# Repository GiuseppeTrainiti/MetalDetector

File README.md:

# MetalDetector

In order to open the code you need to have MDK-ARM Keil installed.
Once you install it, you can open the project:

Metaldetector/Code/Metaldetector/MDK-ARM/metalDetector_comInterface.uvprojx

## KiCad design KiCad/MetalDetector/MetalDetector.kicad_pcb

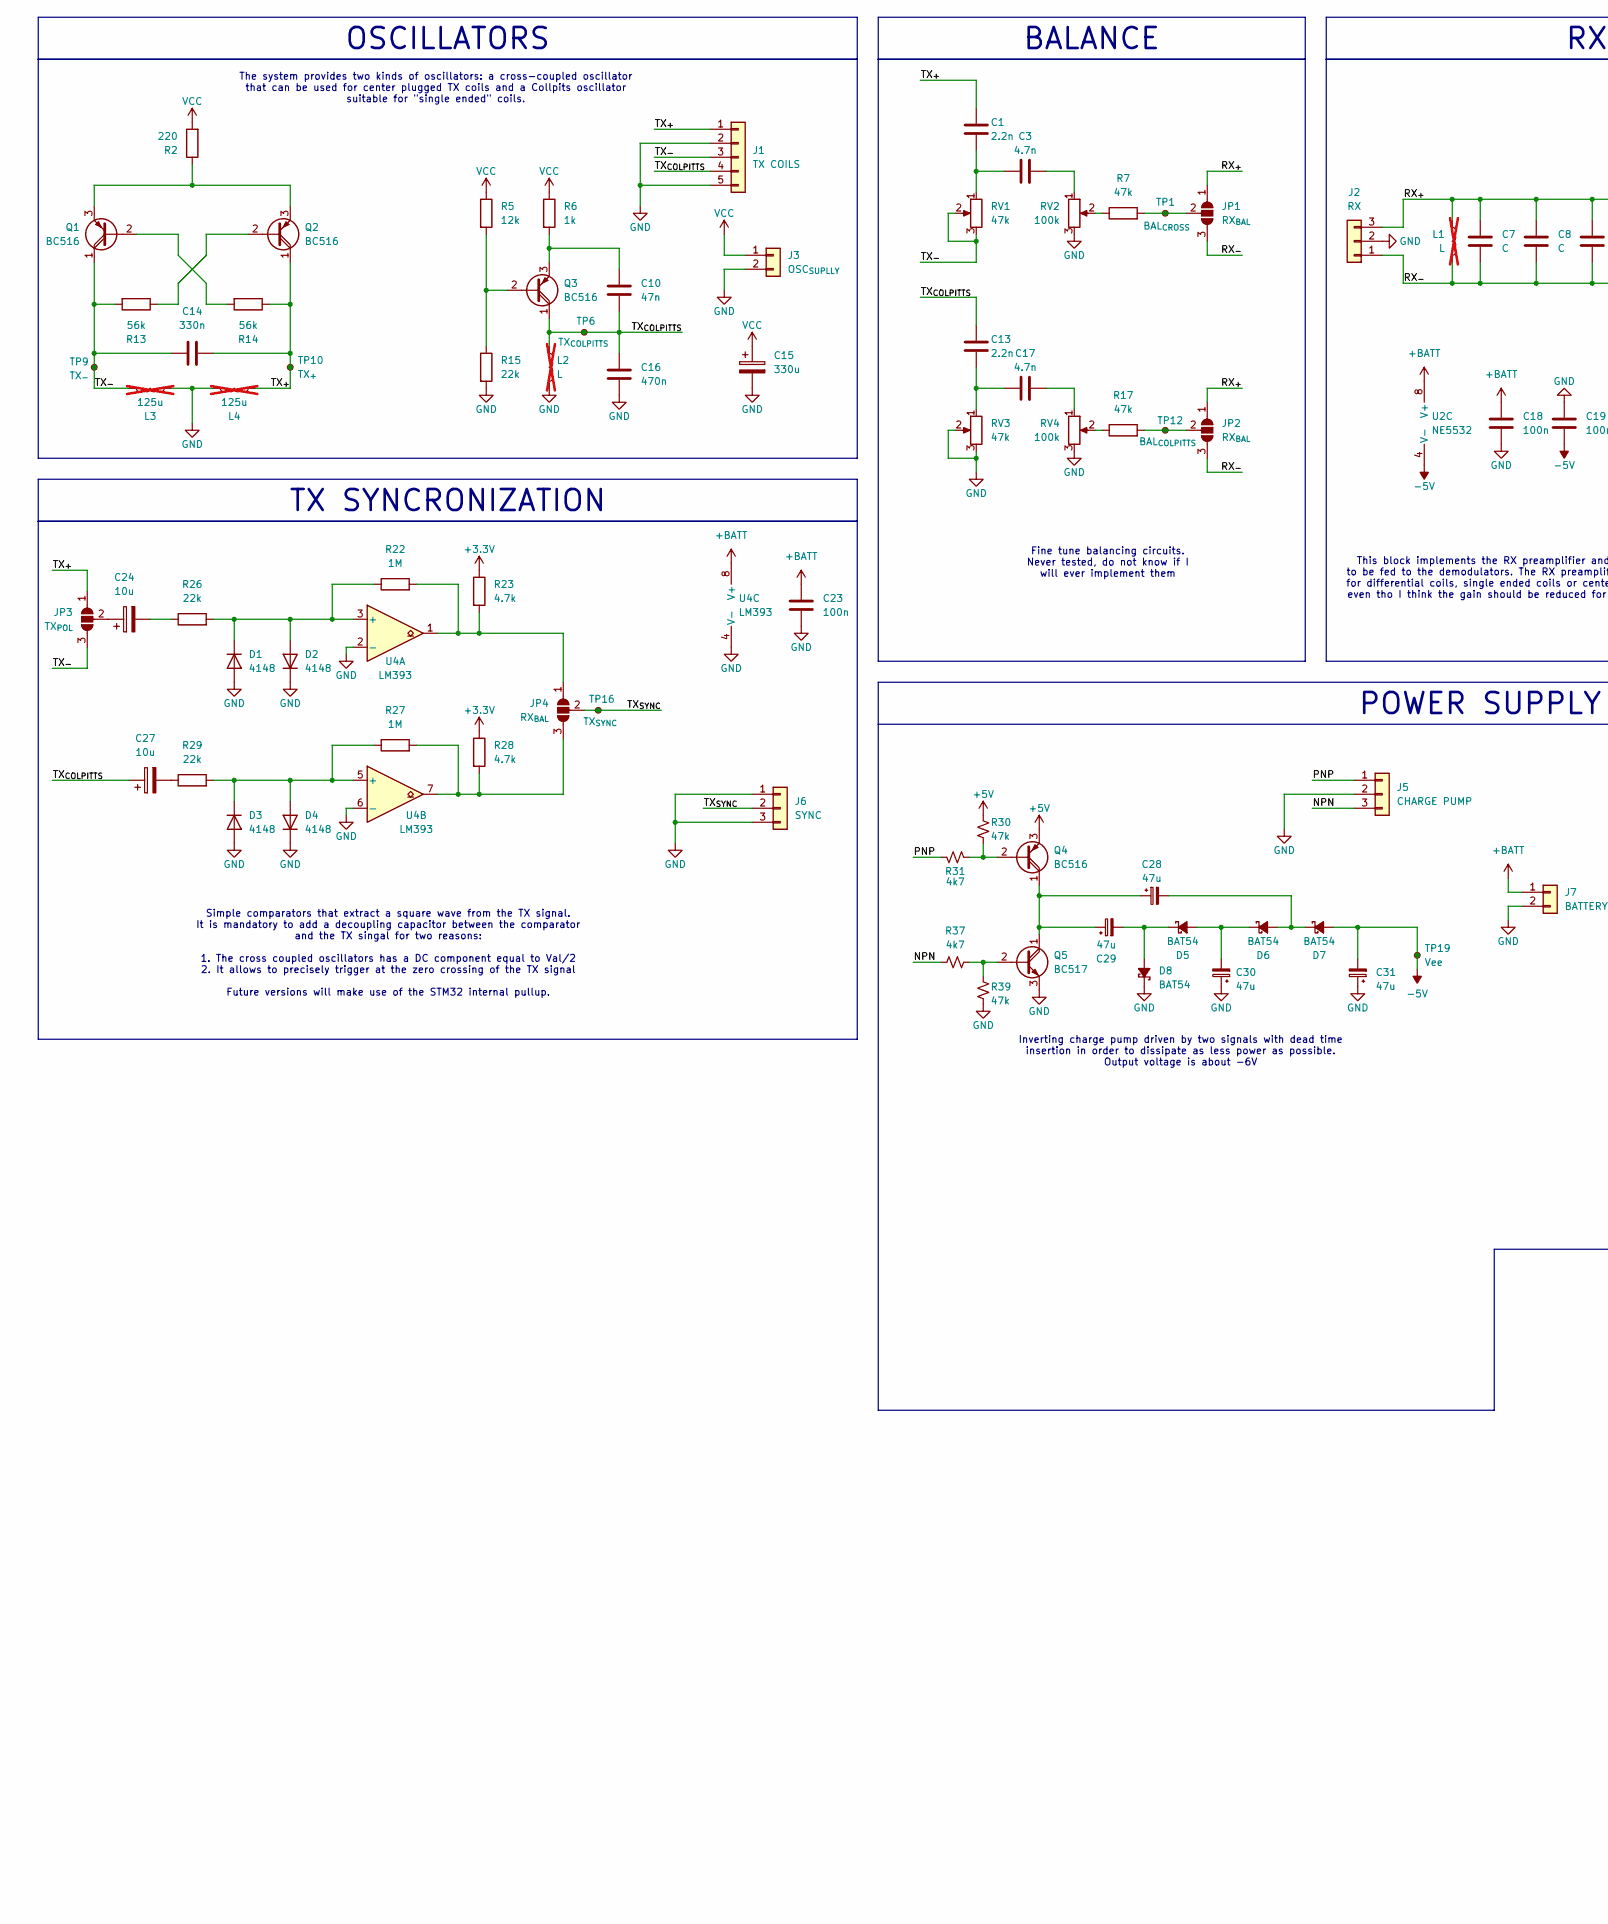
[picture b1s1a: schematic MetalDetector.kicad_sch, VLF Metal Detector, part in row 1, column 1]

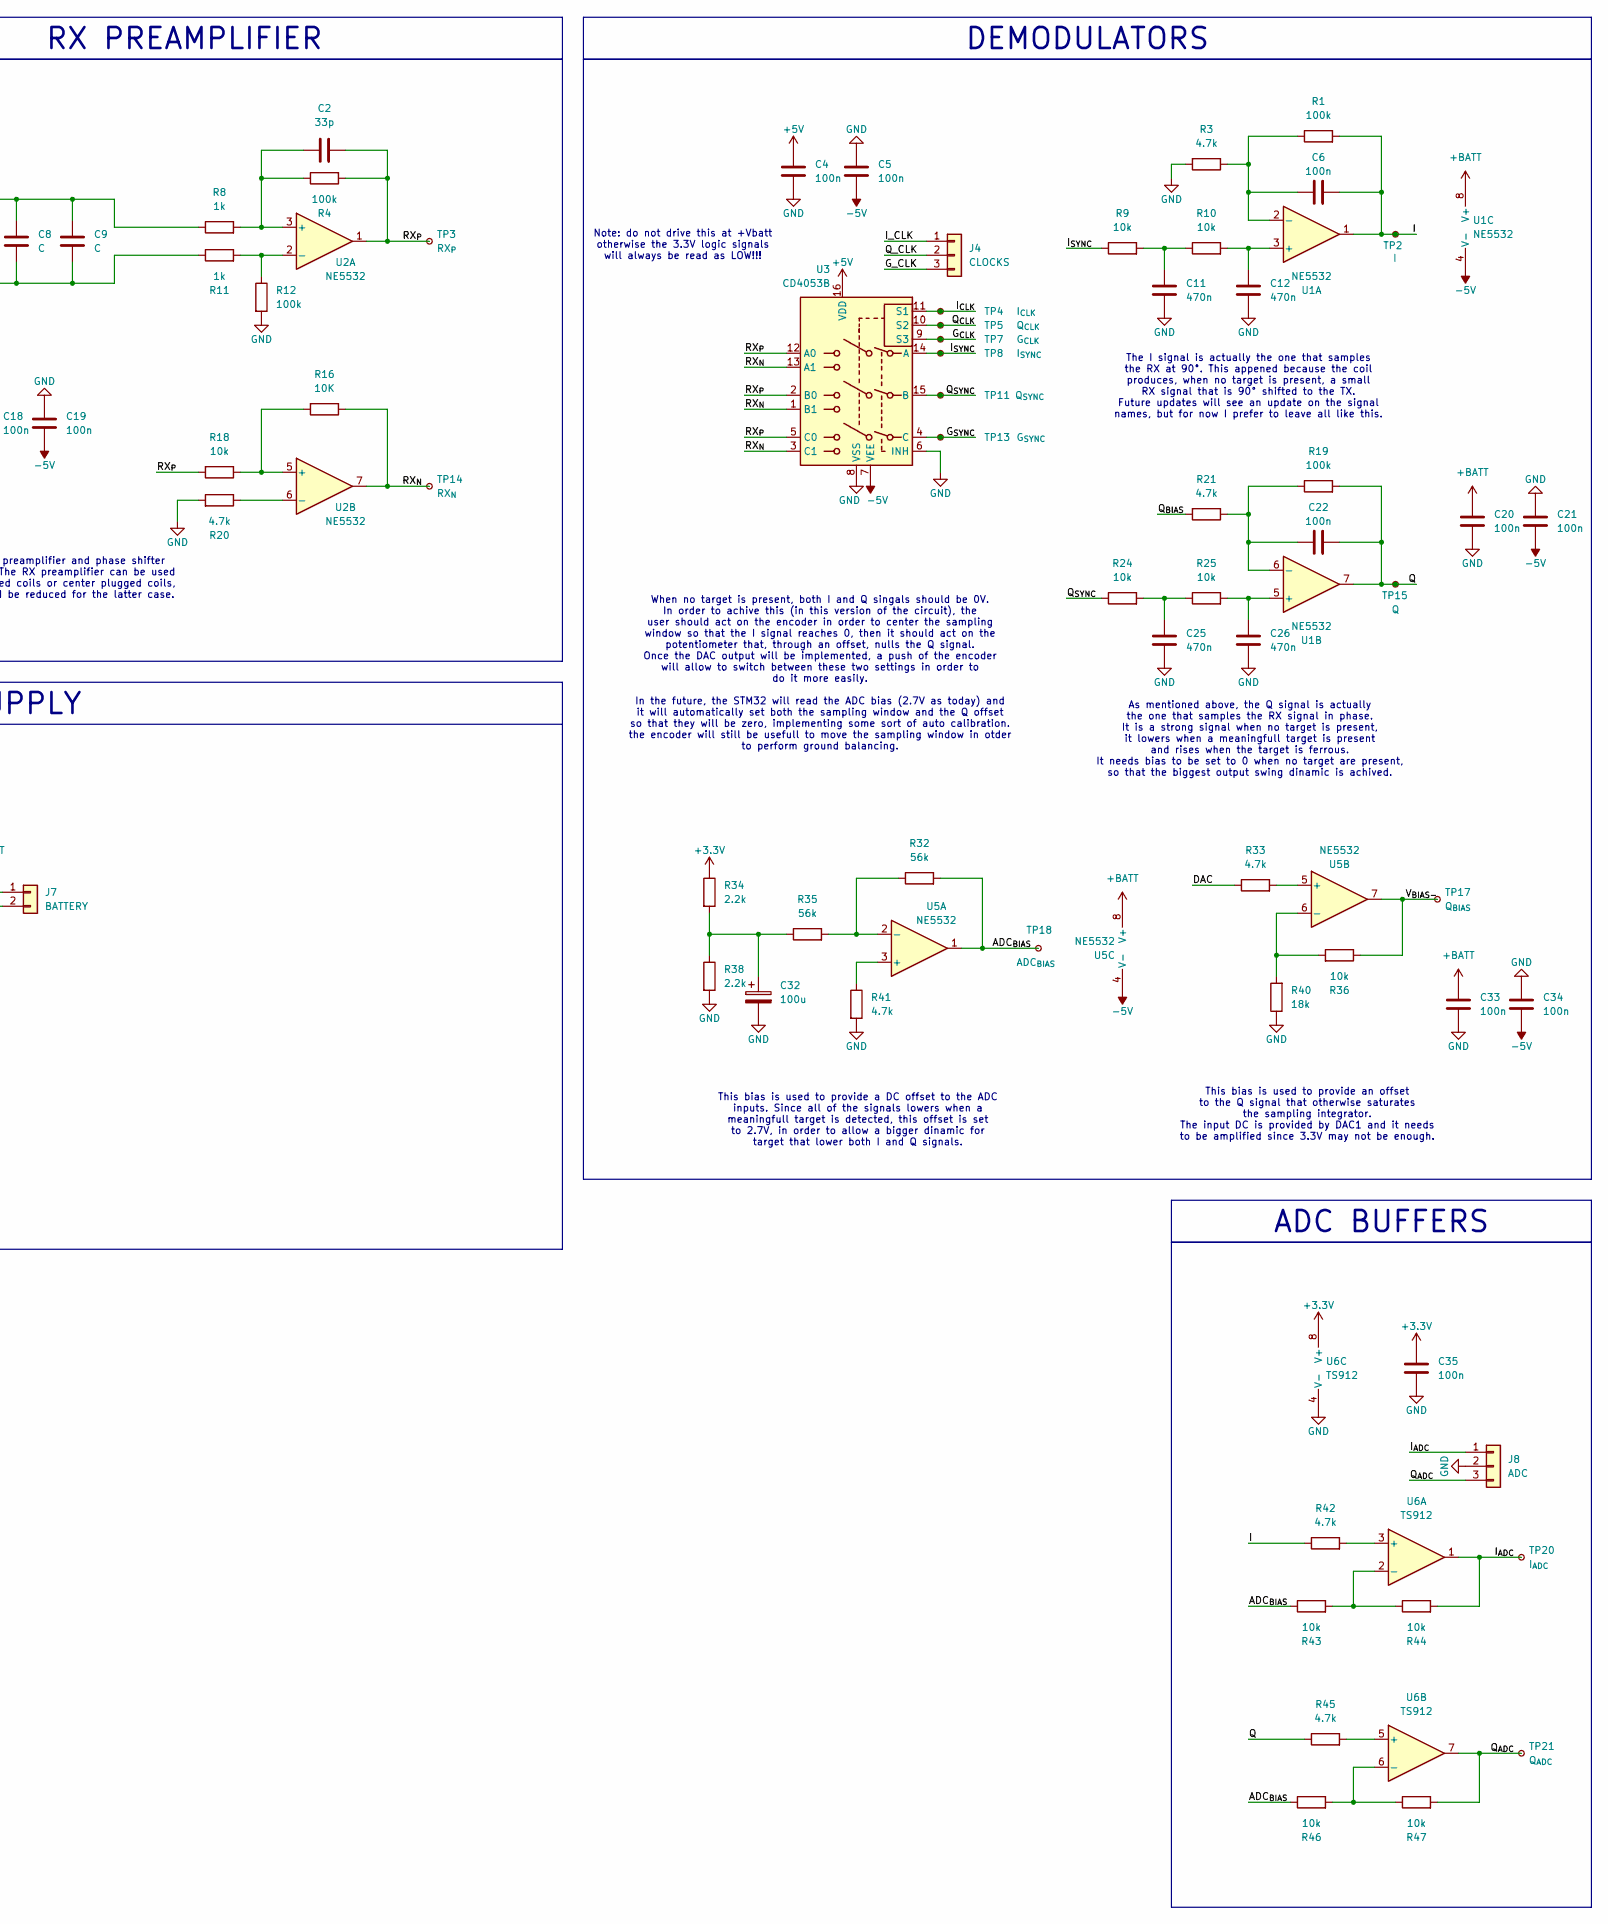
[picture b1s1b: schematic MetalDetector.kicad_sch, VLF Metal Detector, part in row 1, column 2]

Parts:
C1, C13: 2.2n; C_0603_1608Metric_Pad1.08x0.95mm_HandSolder
C2: 33p; C_0603_1608Metric_Pad1.08x0.95mm_HandSolder
C3, C17: 4.7n; C_0603_1608Metric_Pad1.08x0.95mm_HandSolder
C4, C5, C6, C18, C19, C20, C21, C22, C23, C33, C34, C35: 100n; C_0603_1608Metric_Pad1.08x0.95mm_HandSolder
C7, C8, C9: C; C_0603_1608Metric_Pad1.08x0.95mm_HandSolder
C10: 47n; C_0603_1608Metric_Pad1.08x0.95mm_HandSolder
C11, C12, C25, C26: 470n; C_0603_1608Metric_Pad1.08x0.95mm_HandSolder
C14: 330n; C_1812_4532Metric_Pad1.57x3.40mm_HandSolder
C15: 330u; CP_Elec_16x22
C16: 470n; C_1206_3216Metric_Pad1.33x1.80mm_HandSolder
C24, C27: 10u; CP_Elec_5x5.4
C28, C29, C30, C31: 47u; CP_Elec_5x5.4
C32: 100u; CP_Elec_5x5.4
D1, D2, D3, D4: 4148; D_SOD-323F
D5, D6, D7, D8: BAT54; D_SOD-323F
J1: TX COILS
J2: RX
J3: OSC_{SUPLLY}
J4: CLOCKS
J5: CHARGE PUMP
J6: SYNC
J7: BATTERY
J8: ADC
JP1, JP2, JP4: RX_{BAL}; SolderJumper-3_P1.3mm_Open_RoundedPad1.0x1.5mm
JP3: TX_{POL}; SolderJumper-3_P1.3mm_Open_RoundedPad1.0x1.5mm
L1, L2: L; not fitted
L3, L4: 125u; not fitted
Q1, Q2, Q3: BC516; TO-92
Q4: BC516; SOT-23-3
Q5: BC517; SOT-23-3
R1, R4, R12, R19: 100k; R_0603_1608Metric_Pad0.98x0.95mm_HandSolder
R2: 220; R_1206_3216Metric_Pad1.30x1.75mm_HandSolder
R3, R20, R21, R23, R28, R33, R41, R42, R45: 4.7k; R_0603_1608Metric_Pad0.98x0.95mm_HandSolder
R5: 12k; R_0603_1608Metric_Pad0.98x0.95mm_HandSolder
R6: 1k; R_1206_3216Metric_Pad1.30x1.75mm_HandSolder
R7, R17, R30, R39: 47k; R_0603_1608Metric_Pad0.98x0.95mm_HandSolder
R8, R11: 1k; R_0603_1608Metric_Pad0.98x0.95mm_HandSolder
R9, R10, R18, R24, R25, R36, R43, R44, R46, R47: 10k; R_0603_1608Metric_Pad0.98x0.95mm_HandSolder
R13, R14, R32, R35: 56k; R_0603_1608Metric_Pad0.98x0.95mm_HandSolder
R15, R26, R29: 22k; R_0603_1608Metric_Pad0.98x0.95mm_HandSolder
R16: 10K; R_0603_1608Metric_Pad0.98x0.95mm_HandSolder
R22, R27: 1M; R_0603_1608Metric_Pad0.98x0.95mm_HandSolder
R31, R37: 4k7; R_0603_1608Metric_Pad0.98x0.95mm_HandSolder
R34, R38: 2.2k; R_0603_1608Metric_Pad0.98x0.95mm_HandSolder
R40: 18k; R_0603_1608Metric_Pad0.98x0.95mm_HandSolder
RV1, RV3: 47k; Potentiometer_Bourns_3269W_Vertical
RV2, RV4: 100k; Potentiometer_Bourns_3269W_Vertical
TP1: BAL_{CROSS}; TestPoint_Keystone_5010-5014_Multipurpose
TP2: I; TestPoint_Keystone_5010-5014_Multipurpose
TP3: RX_{P}; TestPoint_Keystone_5010-5014_Multipurpose
TP4: I_{CLK}; TestPoint_Keystone_5010-5014_Multipurpose
TP5: Q_{CLK}; TestPoint_Keystone_5010-5014_Multipurpose
TP6: TX_{COLPITTS}; TestPoint_Keystone_5010-5014_Multipurpose
TP7: G_{CLK}; TestPoint_Keystone_5010-5014_Multipurpose
TP8: I_{SYNC}; TestPoint_Keystone_5010-5014_Multipurpose
TP9: TX_{-}; TestPoint_Keystone_5010-5014_Multipurpose
TP10: TX_{+}; TestPoint_Keystone_5010-5014_Multipurpose
TP11: Q_{SYNC}; TestPoint_Keystone_5010-5014_Multipurpose
TP12: BAL_{COLPITTS}; TestPoint_Keystone_5010-5014_Multipurpose
TP13: G_{SYNC}; TestPoint_Keystone_5010-5014_Multipurpose
TP14: RX_{N}; TestPoint_Keystone_5010-5014_Multipurpose
TP15: Q; TestPoint_Keystone_5010-5014_Multipurpose
TP16: TX_{SYNC}; TestPoint_Keystone_5010-5014_Multipurpose
TP17: Q_{BIAS}; TestPoint_Keystone_5010-5014_Multipurpose
TP18: ADC_{BIAS}; TestPoint_Keystone_5010-5014_Multipurpose
TP19: Vee; TestPoint_Keystone_5010-5014_Multipurpose
TP20: I_{ADC}; TestPoint_Keystone_5010-5014_Multipurpose
TP21: Q_{ADC}; TestPoint_Keystone_5010-5014_Multipurpose
U1, U2, U5: NE5532; SOIC-8_3.9x4.9mm_P1.27mm
U3: CD4053B; SOIC-16_3.9x9.9mm_P1.27mm
U4: LM393; SOIC-8_3.9x4.9mm_P1.27mm
U6: TS912; SOIC-8_3.9x4.9mm_P1.27mm

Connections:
+3.3V: C35.1, R23.1, R28.1, R34.1, U6.8 (V+)
+5V: C4.1, Q4.3 (E), R30.1, U3.16 (VDD)
+BATT: C18.1, C20.1, C23.1, C33.1, J7.1, U1.8 (V+), U2.8 (V+), U4.8 (V+), U5.8 (V+)
-5V: C5.2, C19.2, C21.2, C31.2, C34.2, D7.2 (A), TP19.1, U1.4 (V-), U2.4 (V-), U3.7 (VEE), U5.4 (V-)
/ADC_{BIAS}: R32.2, R43.1, R46.1, TP18.1, U5.1
/DAC: R33.1
/G_{CLK}: TP7.1, U3.9 (S3)
/G_{SYNC}: TP13.1, U3.4 (C)
/I: C6.2, R1.2, R42.1, TP2.1, U1.1
/I_{ADC}: J8.1, R44.2, TP20.1, U6.1
/I_{CLK}: TP4.1, U3.11 (S1)
/I_{SYNC}: R9.1, TP8.1, U3.14 (A)
/NPN: J5.3, R37.1
/PNP: J5.1, R31.1
/Q: C22.2, R19.2, R45.1, TP15.1, U1.7
/Q_{ADC}: J8.3, R47.2, TP21.1, U6.7
/Q_{BIAS}: R21.2
/Q_{CLK}: TP5.1, U3.10 (S2)
/Q_{SYNC}: R24.1, TP11.1, U3.15 (B)
/RX_{+}: C7.1, C8.1, C9.1, J2.3, JP1.1 (A), JP2.1 (A), L1.1, R8.1
/RX_{-}: C7.2, C8.2, C9.2, J2.1, JP1.3 (B), JP2.3 (B), L1.2, R11.1
/RX_{N}: R16.1, TP14.1, U2.7, U3.1 (B1), U3.3 (C1), U3.13 (A1)
/RX_{P}: C2.2, R4.2, R18.2, TP3.1, U2.1, U3.2 (B0), U3.5 (C0), U3.12 (A0)
/TX_{+}: C1.1, C14.1, J1.1, JP3.1 (A), L4.1, Q2.1 (C), R14.1, TP10.1
/TX_{-}: C14.2, J1.3, JP3.3 (B), L3.2, Q1.1 (C), R13.2, RV1.2, RV1.3, TP9.1
/TX_{COLPITTS}: C10.2, C13.1, C16.1, C27.1, J1.4, L2.1, Q3.1 (C), TP6.1
/TX_{SYNC}: J6.2, JP4.2 (C), TP16.1
/V_{BIAS-}: R36.1, TP17.1, U5.7
GND: C4.2, C5.1, C11.2, C12.2, C15.2, C16.2, C18.2, C19.1, C20.2, C21.1, C23.2, C25.2, C26.2, C30.1, C31.1, C32.2, C33.2, C34.1, C35.2, D1.2 (A), D2.1 (K), D3.2 (A), D4.1 (K), D8.1 (K), J1.2, J1.5, J2.2, J3.2, J5.2, J6.1, J6.3, J7.2, J8.2, L2.2, L3.1, L4.2, Q5.3 (E), R3.2, R12.2, R15.2, R20.2, R38.2, R39.2, R40.1, R41.2, RV2.3, RV3.2, RV3.3, RV4.3, U3.6 (INH), U3.8 (VSS), U4.2 (-), U4.4 (V-), U4.6 (-), U6.4 (V-)
unnamed: C1.2, C3.1, RV1.1
unnamed: C3.2, RV2.1
unnamed: C11.1, R9.2, R10.1
unnamed: C13.2, C17.1, RV3.1
unnamed: C17.2, RV4.1
unnamed: C24.2, R26.1
unnamed: C25.1, R24.2, R25.1
unnamed: C27.2, R29.1
unnamed: C32.1, R34.2, R35.1, R38.1
unnamed: D1.1 (K), D2.2 (A), R22.1, R26.2, U4.3 (+)
unnamed: D3.1 (K), D4.2 (A), R27.1, R29.2, U4.5 (+)
unnamed: C30.2, D5.2 (A), D6.1 (K)
unnamed: C29.2, D5.1 (K), D8.2 (A)
unnamed: C28.2, D6.2 (A), D7.1 (K)
unnamed: JP1.2 (C), R7.2, TP1.1
unnamed: JP2.2 (C), R17.2, TP12.1
unnamed: C24.1, JP3.2 (C)
unnamed: JP4.1 (A), R22.2, R23.2, U4.1
unnamed: JP4.3 (B), R27.2, R28.2, U4.7
unnamed: Q1.2 (B), R14.2
unnamed: Q1.3 (E), Q2.3 (E), R2.1
unnamed: Q2.2 (B), R13.1
unnamed: Q3.2 (B), R5.2, R15.1
unnamed: C10.1, Q3.3 (E), R6.2
unnamed: Q4.2 (B), R30.2, R31.2
unnamed: C28.1, C29.1, Q4.1 (C), Q5.1 (C)
unnamed: Q5.2 (B), R37.2, R39.1
unnamed: R7.1, RV2.2
unnamed: R17.1, RV4.2
unnamed: C12.1, R10.2, U1.3 (+)
unnamed: C6.1, R1.1, R3.1, U1.2 (-)
unnamed: C26.1, R25.2, U1.5 (+)
unnamed: C22.1, R19.1, R21.1, U1.6 (-)
unnamed: C2.1, R4.1, R8.2, U2.3 (+)
unnamed: R11.2, R12.1, U2.2 (-)
unnamed: R16.2, R18.1, U2.5 (+)
unnamed: R20.1, U2.6 (-)
unnamed: R41.1, U5.3 (+)
unnamed: R32.1, R35.2, U5.2 (-)
unnamed: R33.2, U5.5 (+)
unnamed: R36.2, R40.2, U5.6 (-)
unnamed: R42.2, U6.3 (+)
unnamed: R43.2, R44.1, U6.2 (-)
unnamed: R45.2, U6.5 (+)
unnamed: R46.2, R47.1, U6.6 (-)
VCC: C15.1, J3.1, R2.2, R5.1, R6.1

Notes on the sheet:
This bias is used to provide an offset to the Q signal that otherwise saturates the sampling integrator. The input DC is provided by DAC1 and it needs to be amplified since 3.3V may not be enough.
When no target is present, both I and Q singals should be 0V. In order to achive this (in this version of the circuit), the user should act on the encoder in order to center the sampling window so that the I signal reaches 0, then it should act on the potentiometer that, through an offset, nulls th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
Simple comparators that extract a square wave from the TX signal. It is mandatory to add a decoupling capacitor between the comparator and the TX singal for two reasons: 1. The cross coupled oscillators has a DC component equal to Val/2 2. It allows to precisely trigger at the zero crossing of the 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
The system provides two kinds of oscillators: a cross-coupled oscillator that can be used for center plugged TX coils and a Collpits oscillator suitable for "single ended" coils.
This block implements the RX preamplifier and phase shifter to be fed to the demodulators. The RX preamplifier can be used for differential coils, single ended coils or center plugged coils, even tho I think the gain should be reduced for the latter case.
This bias is used to provide a DC offset to the ADC inputs. Since all of the signals lowers when a meaningfull target is detected, this offset is set to 2.7V, in order to allow a bigger dinamic for target that lower both I and Q signals.
Fine tune balancing circuits. Never tested, do not know if I will ever implement them
The I signal is actually the one that samples the RX at 90°. This appened because the coil produces, when no target is present, a small RX signal that is 90° shifted to the TX. Future updates will see an update on the signal names, but for now I prefer to leave all like this.
Inverting charge pump driven by two signals with dead time insertion in order to dissipate as less power as possible. Output voltage is about -6V
Note: do not drive this at +Vbatt otherwise the 3.3V logic signals will always be read as LOW!!!
As mentioned above, the Q signal is actually the one that samples the RX signal in phase. It is a strong signal when no target is present, it lowers when a meaningfull target is present and rises when the target is ferrous. It needs bias to be set to 0 when no target are present, so that the bigges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
ADC BUFFERS
RX PREAMPLIFIER
POWER SUPPLY
OSCILLATORS
TX SYNCRONIZATION
DEMODULATORS
BALANCE

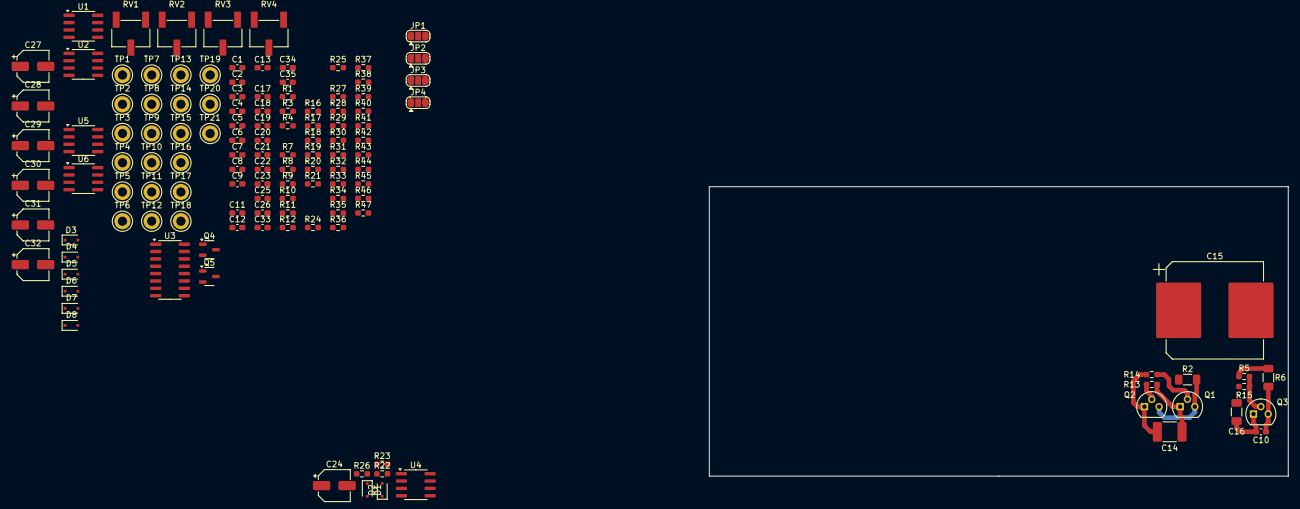
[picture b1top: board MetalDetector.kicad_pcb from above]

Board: 4 copper layers, 100.0 x 50.0 mm, 130 parts (0 on the bottom side), 71 nets.

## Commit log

2025-03-29 First push
2025-03-29 Push
2025-03-30 Push
    Added test points to schematic
2025-03-30 Push
    ADC averages
2025-03-30 Push
    Kicad footprint assignment
2025-03-31 Push
    Test on self calibration at power on
2025-03-31 Push
    Debugging of autoset
2025-04-04 Inline calibration
